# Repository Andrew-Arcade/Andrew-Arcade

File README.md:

Check out my progress in the [journal](JOURNAL.md)!

<!-- ### About Andrew Arcade

Andrew Arcade is a custom game console built with a Raspberry Pi 5 running Linux. Its main purpose is to play Unity games that I have created.

Since the Raspberry Pi 5 uses an ARM processor, Unity games can't be compiled to run on it directly. To solve this, we use a tool called Box64, which lets us run Unity games and apps on the Raspberry Pi by emulating the required architecture.

### Version 2

Version 2 of Andrew Arcade will feature a redesigned case. My goal is to make it more comfortable to use and to improve some of the mounting parts that didn’t work well in the first version. -->

## About the Project

Custom game console designed to run my Unity games.

Designed on top of the Raspberry Pi 5 running pios.

We use [box64](https://github.com/ptitSeb/box64) to run Unity games on the ARM architecture. 

## Apps
[Andrew-Arcade-Apps](https://github.com/AndrewCromar/Andrew-Arcade-Apps) (referred to as "apps repository")
> Most up to date information will be in the apps repository eventually.

### How to contribute your app

To create your own app, you'll need to submit all the source code (the full Unity project) to the apps repository. You will also need to modify the driver app to include your app (details will be provided later). Once your app is ready for release, submit a pull request (PR) to the apps repository. After your PR is approved, you can build the app and submit a second PR to this main Andrew Arcade repository.

### App file structure

Go to the [software/apps](software/apps) directory and create a new folder. Name the folder after your app using camelCase (no spaces, capitalize the first letter of each new word except for the first one). Then, place your app's build files inside the folder you just created.

### Why maintain a second repository?

Unity projects typically require a large amount of storage, while Raspberry Pi 5 devices often have limited space. As a result, the source code for the apps doesn't need to be stored directly on the device.

### More app information

For additional details about the apps or games, check out the [Andrew Arcade Apps](https://github.com/AndrewCromar/Andrew-Arcade-Apps) repository.

## BOM
> [!WARNING]
> I need to update this it is not correct atm.

- You will want an assortment of M3 screws.
- You will need to order your own pcbs (manufacturing files/instructions will come later).

| Name                  | URL                                                                                                    | Notes                                                                                                   |
|-----------------------|--------------------------------------------------------------------------------------------------------|---------------------------------------------------------------------------------------------------------|
| Raspberry Pi 5        | [link](https://www.raspberrypi.com/products/raspberry-pi-5/) | |
| Waveshare RP2040-Zero | [link](https://www.amazon.com/dp/B09L4YNNQH?ref_=cm_sw_r_cp_ud_ct_66QWR2T5E030FK6R5A1J_3&th=1) | Purchase with headers pre-soldered for easier assembly.                                                 |
| Adafruit HDMI Display | [link](https://www.adafruit.com/product/2232) | - Resolution: 800x480.<br> - Size: 5 inches.                                              |
| Buttons               | [link](https://www.amazon.com/dp/B08R9P3RKM?ref_=cm_sw_r_cp_ud_ct_66QWR2T5E030FK6R5A1J_6&th=1) | You need at least 11 buttons. You do not want them to be pre-wired. |
| Joysticks             | [link](https://www.adafruit.com/product/512) | Soldering is required for assembly. |
| 90 Degree Headers     | [link](https://www.amazon.com/PATIKIL-Header-Single-2-54mm-Plated/dp/B0C81QTKC5?source=ps-sl-shoppingads-lpcontext&ref_=fplfs&gQT=1&th=1) | Used to connect the joysticks to the board. |
| Button Wires          | [link](https://www.amazon.com/dp/B092CW94LK?ref_=cm_sw_r_cp_ud_ct_66QWR2T5E030FK6R5A1J_5&th=1) | You need at least 11. |
| JST Connectors        | [link](https://www.amazon.com/dp/B0B2R966ZY?ref_=cm_sw_r_cp_ud_ct_66QWR2T5E030FK6R5A1J_4&th=1) | - Size: 2P.<br> - Style: XH.

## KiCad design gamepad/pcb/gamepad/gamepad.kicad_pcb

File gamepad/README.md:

# How to build your gamepad.

> I may make a better version of these instructions later.

1. Gather parts.
    - Get a Raspberry Pi Pico.
    - Get six buttons.
    - Get a joystick module.
2. Wire it according to the schematic.
    - pcb/schematic.pdf
3. Install the firmware.
    - _firmware/GP2040-CE_0.7.10_Pico.uf2
4. Set the pin mappings for the controller according to my image.
    - pin-mappings.png
5. Done! You should have six buttons and the joystick.

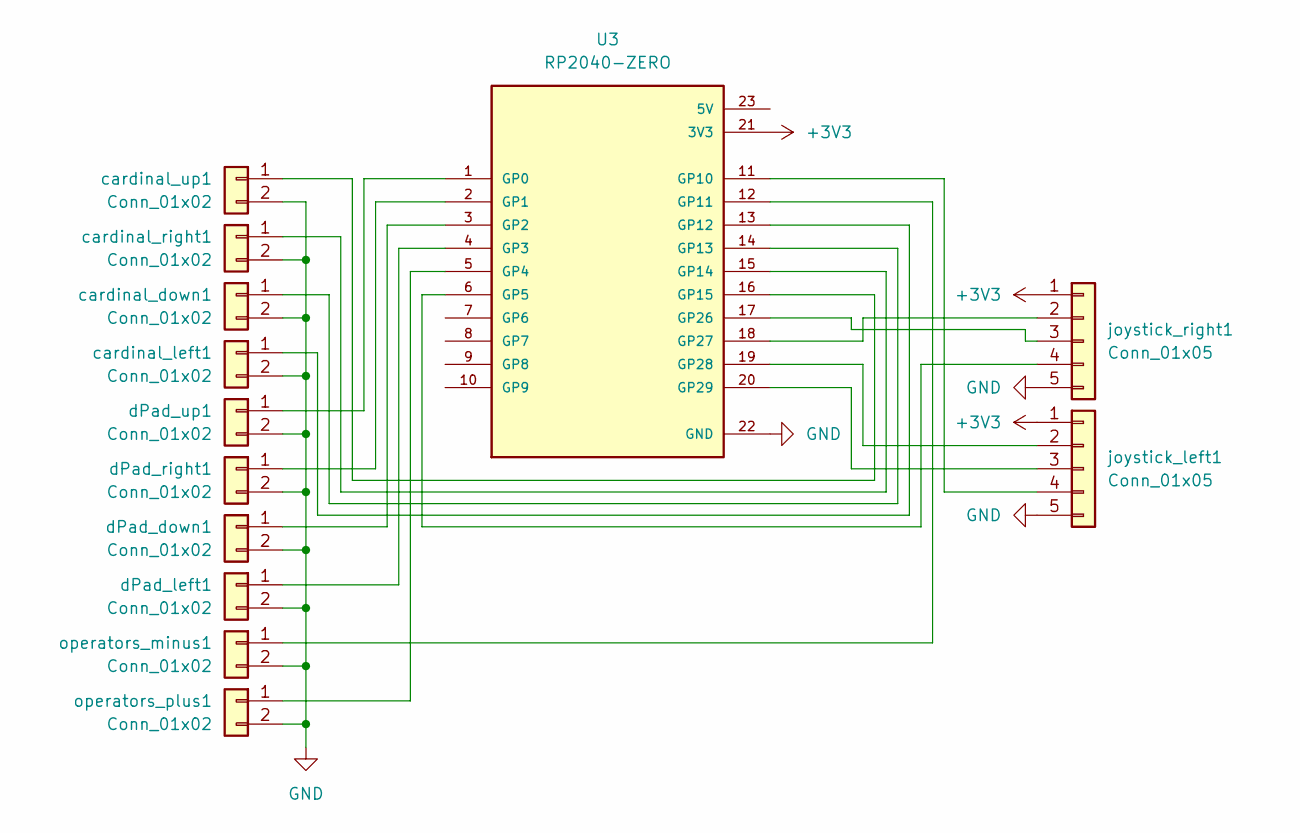
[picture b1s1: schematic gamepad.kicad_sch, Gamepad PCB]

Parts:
U3: RP2040-ZERO; MODULE_RP2040-ZERO; PARTREV NA
cardinal_down1: Conn_01x02; JST_XH_B2B-XH-A_1x02_P2.50mm_Vertical
cardinal_left1: Conn_01x02; JST_XH_B2B-XH-A_1x02_P2.50mm_Vertical
cardinal_right1: Conn_01x02; JST_XH_B2B-XH-A_1x02_P2.50mm_Vertical
cardinal_up1: Conn_01x02; JST_XH_B2B-XH-A_1x02_P2.50mm_Vertical
dPad_down1: Conn_01x02; JST_XH_B2B-XH-A_1x02_P2.50mm_Vertical
dPad_left1: Conn_01x02; JST_XH_B2B-XH-A_1x02_P2.50mm_Vertical
dPad_right1: Conn_01x02; JST_XH_B2B-XH-A_1x02_P2.50mm_Vertical
dPad_up1: Conn_01x02; JST_XH_B2B-XH-A_1x02_P2.50mm_Vertical
joystick_left1: Conn_01x05; JST_PH_B5B-PH-K_1x05_P2.00mm_Vertical
joystick_right1: Conn_01x05; JST_PH_B5B-PH-K_1x05_P2.00mm_Vertical
operators_minus1: Conn_01x02; JST_XH_B2B-XH-A_1x02_P2.50mm_Vertical
operators_plus1: Conn_01x02; JST_XH_B2B-XH-A_1x02_P2.50mm_Vertical

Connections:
+3V3: U3.21 (3V3), joystick_left1.1, joystick_right1.1
GND: U3.22 (GND), cardinal_down1.2, cardinal_left1.2, cardinal_right1.2, cardinal_up1.2, dPad_down1.2, dPad_left1.2, dPad_right1.2, dPad_up1.2, joystick_left1.5, joystick_right1.5, operators_minus1.2, operators_plus1.2
unnamed: U3.1 (GP0), dPad_up1.1
unnamed: U3.2 (GP1), dPad_right1.1
unnamed: U3.3 (GP2), dPad_down1.1
unnamed: U3.4 (GP3), dPad_left1.1
unnamed: U3.5 (GP4), operators_plus1.1
unnamed: U3.6 (GP5), joystick_right1.4
unnamed: U3.11 (GP10), joystick_left1.4
unnamed: U3.12 (GP11), operators_minus1.1
unnamed: U3.13 (GP12), cardinal_left1.1
unnamed: U3.14 (GP13), cardinal_down1.1
unnamed: U3.15 (GP14), cardinal_right1.1
unnamed: U3.16 (GP15), cardinal_up1.1
unnamed: U3.17 (GP26), joystick_right1.3
unnamed: U3.18 (GP27), joystick_right1.2
unnamed: U3.19 (GP28), joystick_left1.2
unnamed: U3.20 (GP29), joystick_left1.3

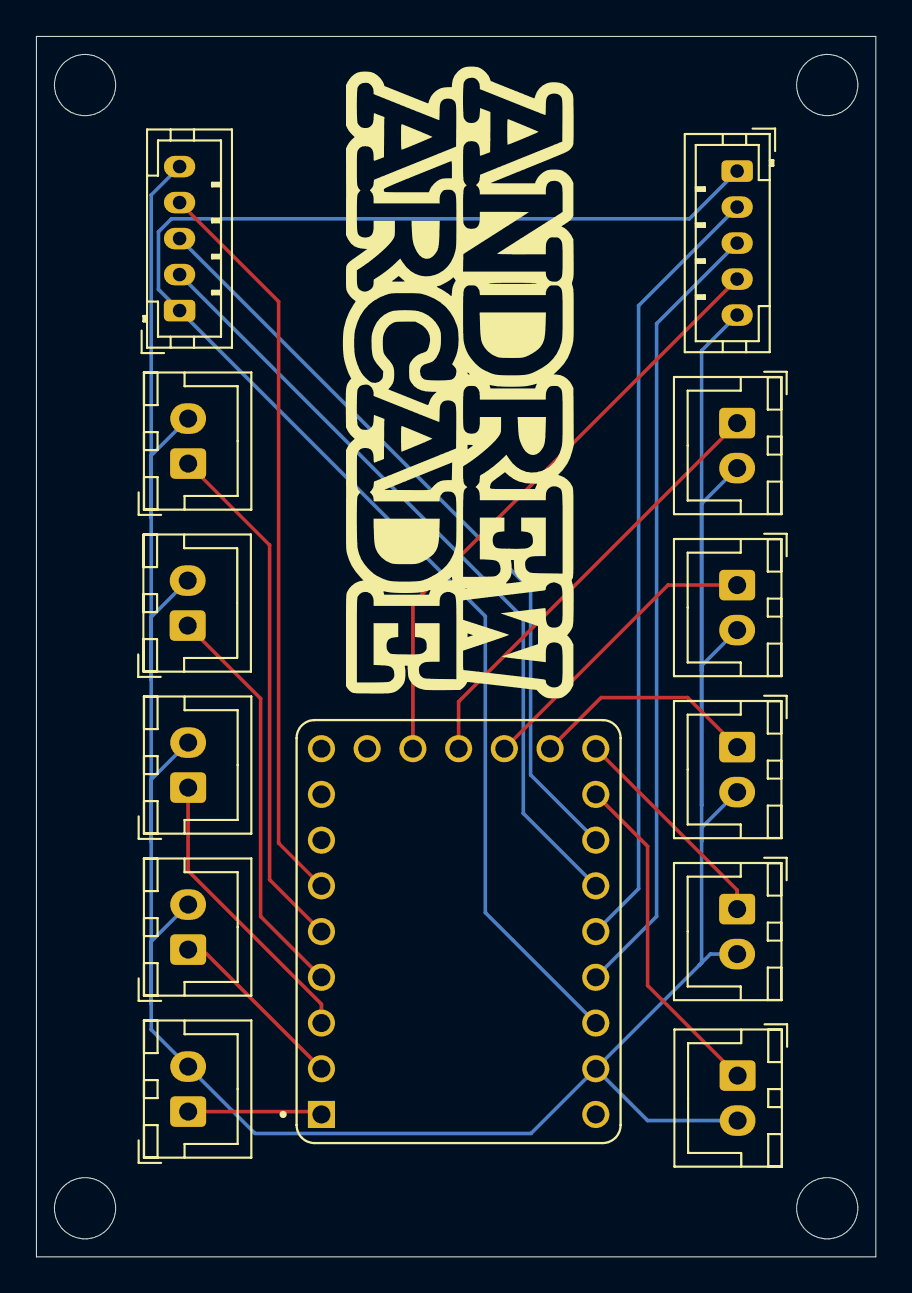
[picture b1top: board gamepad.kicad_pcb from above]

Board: 2 copper layers, 46.6 x 67.8 mm, 13 parts (0 on the bottom side), 18 nets.

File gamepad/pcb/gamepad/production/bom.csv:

Designator,Footprint,Quantity,Value,LCSC Part #
"CARDINAL_DOWN1, CARDINAL_LEFT1, CARDINAL_RIGHT1, CARDINAL_UP1, DPAD_EAST1, DPAD_NORTH1, DPAD_SOUTH1, DPAD_WEST1, OPERATORS_MINUS1, OPERATORS_PLUS1",JST_XH_B2B-XH-A_1x02_P2.50mm_Vertical,10,Conn_01x02,
"JOYSTICK_LEFT1, JOYSTICK_RIGHT1",JST_PH_B5B-PH-K_1x05_P2.00mm_Vertical,2,Conn_01x05,
U3,MODULE_RP2040-ZERO,1,RP2040-ZERO,

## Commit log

2024-09-26 Initial commit.
2024-09-26 feat: add joystick button
    also commented out the calibration variables
2024-09-26 feat(s/poc/docs): work'n on it
2024-09-26 fix(s/poc/docs): update readme
2024-09-26 feat: update joystick calibration readme
2024-09-26 fix: joystick calibration
    change the output file, remove the blinking light
2024-09-26 feat: disable drive
    dont show the drive when controller plugged in
2024-09-26 feat: Update README.md
2024-09-26 remove: keyboard testing
2024-09-26 fix: update readme
2024-09-26 feat: add button to disable the drive hiding
2024-09-26 fix: button to hid drive fix
2024-09-27 feat: add random things to save for future
2024-09-27 feat: working on calibration
2024-09-27 feat: FIXED CALIBRATION!
2024-09-27 remove: calibration output file
2024-09-27 fix: rename the random stuff folder
2024-09-27 fix: update readme to new calibration info
2024-09-29 feat: add more preset folders
2024-10-01 feat: add some modles
2024-10-01 feat: joystick mount v3
2024-10-01 dump: 1
2024-10-01 dump: 2
2024-10-01 dump: 3
2024-10-01 dump: 4
2024-10-01 dump: 5
2024-10-01 dump: 7
2024-10-01 dump: 8
2024-10-01 dump: 9
2024-10-01 dump: 10
2024-10-01 dump: 11
2024-10-02 pcb: working on the pcb
2024-10-02 feat: add flappyturd build
2024-10-02 firmware: add readme
2024-10-02 feat: worked on pcb
2024-10-03 feat: worked on controller firmware
2024-10-03 feat: add new software folder
2024-10-03 feat: reorder some files
2024-10-03 feat: add some photos
    please ignore the long af folder name lol
2024-10-03 feat: add not blurry photo
2024-10-03 feat: made a log
2024-10-03 fix: log
2024-10-04 feat: working on gamepad
2024-10-04 feat: add and update apps
2024-10-04 feat: fixing path
2024-10-04 feat: remove flappy turd
2024-10-04 feat: add flappyTurd
2024-10-04 feat(apps): update driver
2024-10-04 fix: startup.sh
2024-10-04 feat: update driver
2024-10-04 feat: update readme
2024-10-04 fix: changed comment
2024-10-09 feat: finally got the controller working imgame
2024-10-09 feat: working on pcb
2024-10-17 feat(log): add to log
2024-10-17 feat: fix parts list
2024-10-17 feat: working on parts list
2024-10-17 fix: parts.md
2024-10-18 feat(log): add stuff for the log
2024-10-18 fix(log): typo
2024-10-21 feat(log): add images
2024-10-21 feat(log): made the log look better and add dates
2024-10-21 feat(readmy): fixed up the readme
2024-10-21 fix(log): image url typo
2024-10-21 feat(readme): made it look good
2024-10-21 feat(readme): apps info
2024-10-21 feat(readme): add more info about apps
2024-10-21 feat(readme): change wording a bit
2024-10-21 feat(readme): add help thing
2024-10-21 feat(redme): add stuff
2024-10-21 feat(readme): change help
2024-10-22 feat(log): add
2024-10-22 feat(log): add periods
2024-10-23 fix(log): src typo
2024-10-30 feat(modles): add
2024-11-01 feat: update modles
2024-11-02 feat: update models
2024-11-02 fix: folder name typo
2024-11-15 feat: export controller schematic
2024-11-15 feat(log): update
2024-11-16 fix: controller schematic
2024-11-17 fix: controller code
    - reverse +/- buttons
    - negate joystick to have correct directions
2024-11-17 update: apps
    - driver
    - flappyTurd
2024-11-18 fix: gamepad
2024-11-18 fix: driver app
2024-11-18 fix: stuff
2024-11-19 feat: remove v1 modles, add v2
2024-11-21 upd: driver
2024-11-30 feat: build driver
2024-11-30 feat: testing downgraded driver
2024-11-30 feat: test flappy build
2024-11-30 feat: update flappy turd
2024-12-01 feat: build template
2024-12-01 feat: create tester.sh
2024-12-01 feat: build flappy turd
2024-12-01 feat: build turd again
2024-12-01 feat: build some apps
2024-12-01 feat: update controller code
2024-12-01 feat: build tester
2024-12-01 feat: build template 3
2024-12-01 feat: build template 4
2024-12-01 feat: build template 5
2024-12-01 feat: build template 6
2024-12-01 feat: build template 7
2024-12-01 feat: build template 8
2024-12-01 test 9
2024-12-01 test 10
2024-12-01 test 11
2024-12-01 feat: build apps
2024-12-01 feat: gamepad firmware
2024-12-01 upt: software instructions
2024-12-01 upd(software): driver
2024-12-01 upd(software): build some apps
2024-12-02 upd: models
2024-12-07 upt: models
2024-12-07 upt: log
2024-12-11 upd: startup.sh
2024-12-11 fix: startup script
2024-12-11 feat: deck files
2024-12-11 fix: deck file type
2024-12-11 feat: startup script
2024-12-18 upt: deck model
2024-12-18 upt: readmes
2025-01-11 rmv: unused pcb files
2025-01-11 upt(log)
2025-01-11 upt(models): convert to bambu
2025-01-23 upt: schematic
2025-01-23 upd: log
2025-01-23 rmv: schematic auto backup
2025-01-31 upt(models)
2025-02-02 feat(software): build schoolCountdown
2025-02-02 upt(software): driver
2025-02-02 upt(software): hide cursor in some apps
2025-02-02 upt(software): startup.sh
2025-02-02 fix(software): driver binding
2025-02-03 upt(software): schoolCountdown
2025-02-08 add(software): oranyth
2025-02-08 upt(software): add oranyth to startup script
2025-02-08 upt(software): oranyth
2025-02-08 upt(software): trying to fix oranyth
2025-02-08 upt(software): trying to fix oranyth 2
2025-02-08 upt(software): trying to fix oranyth 3
2025-02-08 upt(software): trying to fix oranyth 4
2025-02-08 upt(software): trying to fix oranyth 5
2025-02-08 upt(software): trying to fix oranyth 6
2025-02-08 upt(software): trying to fix oranyth 7
2025-02-08 upt(software): finally fixed oranyth
2025-02-08 upt(software): readme
2025-02-28 upt(software): flappyTurd
2025-03-06 feat: make logo
2025-03-07 put: read me
2025-03-07 upt: readme
2025-03-07 upt: logo
2025-04-10 feat: start v2 todo
2025-04-18 feat: archive software
2025-04-19 rmv: archive
2025-04-19 upt: readme and log
2025-04-19 upt: todo
2025-04-28 feat(software): add some apks
2025-04-28 feat(workflows): add apk index workflow
2025-04-28 feat(workflows): update generate_index script
2025-05-19 rmv: log content moved it to the log repo
2025-05-21 rmv: old pcb
2025-05-21 feat: start work on schematic
2025-05-22 upt(gamepad): working on pcb
2025-05-23 rmv: download dump
2025-05-23 upt: readme.md
2025-05-23 feat: add journal
2025-05-23 fix: file paths
2025-05-24 upt: journal
2025-05-30 upt: gamepad pcb
2025-05-30 upt: start wiring schematic
    just gotta make sure it works on a breadboard before ordering a pcb
2025-05-30 upt: some stuff for the pcb
    - routed the traces
    - cleaned up the wiring for the schematic
2025-05-31 upt: pcb
    add logo
2025-06-02 add: icon files
2025-06-05 feat: some pcb stuff
2025-06-05 upt: pico to waveshare zero
    change out the pcb to have a waveshare zero instead of a pico
2025-06-05 upt: pcb
2025-06-25 fix: readme
2025-06-26 feat: pcb stuff
2025-06-26 upt: parts list
2025-06-26 upt: autostart stuff
2025-07-01 feat: exported pcb files
2025-07-21 feat: smaller pcb
2025-08-10 feat: firmware backup
    to use on other devices to setup the firmware quicker
2025-08-10 fix: swap pcb left/right
2025-10-02 feat: temp add apps instructions
    - to be rewritten/moved later
2025-10-03 feat: add models
2025-10-03 rmv: software - moved to seperate repo
2025-10-03 rmv: driver app instructions
2025-12-01 feat: work on gamepad
2026-05-13 working on simple pcb
2026-05-13 Revert "working on simple pcb"
    This reverts commit e8ce82c8a07d9a8eb121910e16f9c7b1daafe766.
